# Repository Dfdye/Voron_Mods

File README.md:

# Voron_Mods

The parts in this repository have been designed for my own use, and not specifically for public release.  As such, they probably contain multiple errors, and are subject to change without notice.  I may not even change file names (sorry!), so please check the suitability of parts for your applicaiton prior to their use.  In some instances I have based designs off of existing parts.  I may have included copies of these parts in my repositories for the sake of convenience, but I have tried to link to the originals and give proper credit whenever I have done so.  If you notice a part that I did not attribute properly, I assure you this this is an oversight and not an attempt to claim anyone's work as my own. Please let me know if you notice where I have failed to properly attribute and I will get that fixed as soon as possible!

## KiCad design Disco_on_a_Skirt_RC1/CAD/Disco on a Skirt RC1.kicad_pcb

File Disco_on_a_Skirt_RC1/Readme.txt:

This is a silly board that does RGB lights.  It's absurdly simple, so I didn't spend ~~much~~ any time on documentation.  If you want all of the good info, go to Blamm!'s Disco on a Stick documentation.  He actually did the work.  I am just copying what he did and putting it in the shape of a Voron logo.  

The only thing you need to know is that they use the WS2812B-V5/W LEDs.  

https://github.com/VoronDesign/Voron-Hardware/tree/master/Daylight

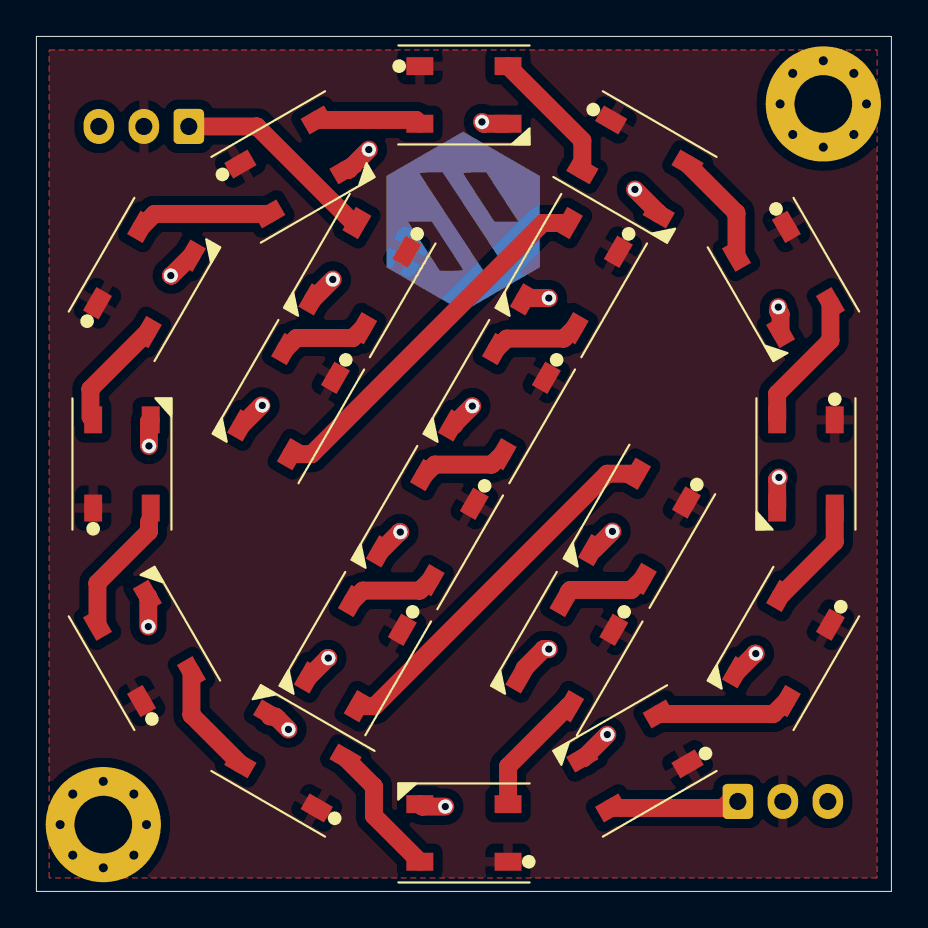
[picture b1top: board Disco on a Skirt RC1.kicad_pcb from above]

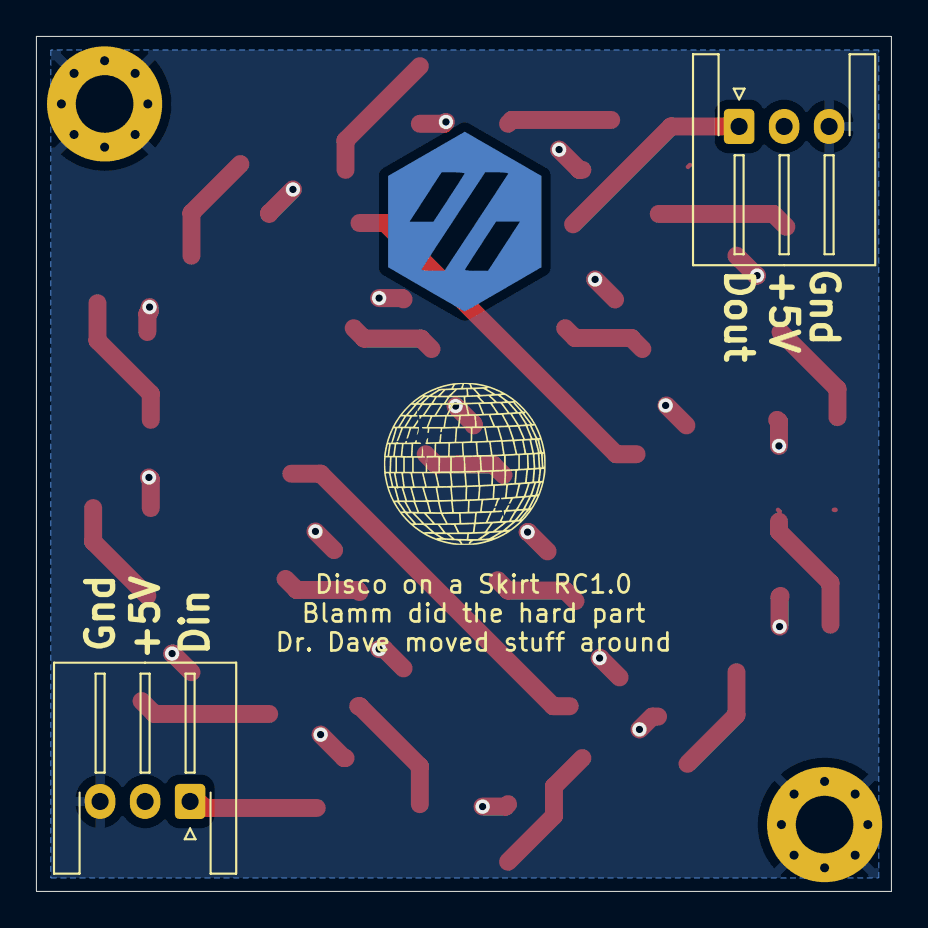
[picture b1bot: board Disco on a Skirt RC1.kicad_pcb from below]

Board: 2 copper layers, 47.5 x 47.5 mm, 24 parts (2 on the bottom side), 23 nets.

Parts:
D1, D2, D3, D4, D5, D6, D7, D8, D9, D10, D11, D12, D13, D14, D15, D16, D17, D18, D19, D20: WS2812B-V5/W; LED_WS2812B_PLCC4_5.0x5.0mm_P3.2mm
H1, H2: MountingHole; MountingHole_3.2mm_M3_Pad_Via
J1, J2: Conn_01x03_Male; JST_XH_S3B-XH-A-1_1x03_P2.50mm_Horizontal

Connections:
+5V: D1.1 (VDD), D2.1 (VDD), D3.1 (VDD), D4.1 (VDD), D5.1 (VDD), D6.1 (VDD), D7.1 (VDD), D8.1 (VDD), D9.1 (VDD), D10.1 (VDD), D11.1 (VDD), D12.1 (VDD), D13.1 (VDD), D14.1 (VDD), D15.1 (VDD), D16.1 (VDD), D17.1 (VDD), D18.1 (VDD), D19.1 (VDD), D20.1 (VDD), J1.2, J2.2
DIN: D1.e (DIN), J1.1
DOUT: D20.2 (DOUT), J2.1
GND: D1.3 (VSS), D2.3 (VSS), D3.3 (VSS), D4.3 (VSS), D5.3 (VSS), D6.3 (VSS), D7.3 (VSS), D8.3 (VSS), D9.3 (VSS), D10.3 (VSS), D11.3 (VSS), D12.3 (VSS), D13.3 (VSS), D14.3 (VSS), D15.3 (VSS), D16.3 (VSS), D17.3 (VSS), D18.3 (VSS), D19.3 (VSS), D20.3 (VSS), H1.1, H2.1, J1.3, J2.3
unnamed: D15.2 (DOUT), D16.4 (DIN)
unnamed: D16.2 (DOUT), D17.4 (DIN)
unnamed: D17.2 (DOUT), D18.4 (DIN)
unnamed: D18.2 (DOUT), D19.4 (DIN)
unnamed: D19.2 (DOUT), D20.4 (DIN)
New3: D14.2 (DOUT), D15.4 (DIN)
new2: D13.2 (DOUT), D14.4 (DIN)
p1: D7.2 (DOUT), D8.4 (DIN)
p2: D8.2 (DOUT), D9.4 (DIN)
p3: D9.2 (DOUT), D10.4 (DIN)
p4: D10.2 (DOUT), D11.4 (DIN)
p5: D11.2 (DOUT), D12.4 (DIN)
p6: D12.2 (DOUT), D13.4 (DIN)
p7: D1.2 (DOUT), D2.4 (DIN)
p8: D2.2 (DOUT), D3.4 (DIN)
p9: D3.2 (DOUT), D4.4 (DIN)
p10: D4.2 (DOUT), D5.4 (DIN)
p11: D5.2 (DOUT), D6.4 (DIN)
p12: D6.2 (DOUT), D7.4 (DIN)

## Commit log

2022-01-09 Rename Nozzle Brush Assembly for Kinematic Mounts and Trident.stp to Purge_Bucket_for_WP_Kinetic_Mount/Nozzle_Brush_Assembly_for_Kinematic_Mounts_and_Trident.stp
2022-01-09 Rename Purge Bucket--Small Vertical.stl to Purge_Bucket_for_WP_Kinetic_Mount/Purge_Bucket--Small_Vertical.stl
2022-01-09 Rename Purge Bucket--Large Vertical.stl to Purge_Bucket_for_WP_Kinetic_Mount/Purge_Bucket--Large_Vertical.stl
2022-01-09 Rename Purge_Bucket_for_WP_Kinetic_Mount/Nozzle_Brush_Assembly_for_Kinematic_Mounts_and_Trident.stp to Purge_Bucket_for_WP_Kinetic_Mount/STLs/Nozzle_Brush_Assembly_for_Kinematic_Mounts_and_Trident.stp
2022-01-09 Rename Purge_Bucket_for_WP_Kinetic_Mount/Purge_Bucket--Large_Vertical.stl to Purge_Bucket_for_WP_Kinetic_Mount/STLs/Purge_Bucket--Large_Vertical.stl
2022-01-09 Rename Purge_Bucket_for_WP_Kinetic_Mount/Purge_Bucket--Small_Vertical.stl to Purge_Bucket_for_WP_Kinetic_Mount/STLs/Purge_Bucket--Small_Vertical.stl
2022-01-09 Rename Purge_Bucket_for_WP_Kinetic_Mount/STLs/Nozzle_Brush_Assembly_for_Kinematic_Mounts_and_Trident.stp to Purge_Bucket_for_WP_Kinetic_Mount/CAD/Nozzle_Brush_Assembly_for_Kinematic_Mounts_and_Triden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
2022-02-11 Added Brush Mount Spacer
2022-02-16 Added brush mount spacer.
2024-02-15 Add a brush holder with no sheet stop.
    This mod is useful when using whopping's universal bed. https://github.com/tanaes/whopping_Voron_mods/tree/main/universal_bed
2024-02-15 Update step file with brush no sheet stop mod.
2024-02-15 Remove old STEP file
2024-02-15 Fix large purge orientation
